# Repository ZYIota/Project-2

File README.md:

# Project-2
This is the Starbie PCB, it is a Printed Circuit Board
It contains multiple components such as the XIAO-ESP32-C3, the MPU-6050 and the DHT11 sensor
I chose to do this project as it was guided and much easier to learn everything from scratch, its relatively low complexity allows me to finish it

This is my PCB layout for the starbie, it contains the electrical wiring and connections for the board (the physical arrangement of components and connectors)
The blue connections means the electrical connections are at the back of the circuit while the red connections means the electrical connections are at the front of the circuit. Connections between components allow communication to occur, hence it is important to connect them according to their ports correctly such as GND to GND and not GND to 5V

This is my schematic layout, it defines the electrical circuit, you can see all the separate components and their pins(GND etc)

This is my 3d layout of the Starbie, it is a render of the PCB layout, it contains the electrical connections and components

FRONT VIEW:

BACK VIEW:

Assembling it requires the pins of correct components matched with the corresponding sections of the PCB, and to physically connect them requires soldering, which uses a soldering iron to melt a solder wire to allow electricity flow while physically sticking to each other

## Bill of Materials (BOM)

| Reference | Qty | Value | Footprint | Datasheet | Price (USD) | Product Link |
|---|---:|---|---|---|---:|---|
| J1 | 1 | Conn_01x04_Pin | Imported Parts:Display_128x64_096_I2C | — | $2.10 | [aliexpress.com/item/1005006141235306.html?spm=a2g0o.cart.0.0.376e38dawU3KcG&mp=1&pdp_npi=6%40dis%21SGD%21SGD%202.89%21SGD%202.69%21%21SGD%202.69%21%21%21%402102ee9117922575991276049e0f0f%2112000035944225406%21ct%21SG%216710596671%21%211%210%21](aliexpress.com/item/1005006141235306.html?spm=a2g0o.cart.0.0.376e38dawU3KcG&mp=1&pdp_npi=6%40dis%21SGD%21SGD%202.89%21SGD%202.69%21%21SGD%202.69%21%21%21%402102ee9117922575991276049e0f0f%2112000035944225406%21ct%21SG%216710596671%21%211%210%21) |
| J2 | 1 | Conn_01x08_Pin | Imported Parts:MPU6050_Module | — | $1.68 | [https://www.aliexpress.com/item/1005010057794277.html?spm=a2g0o.cart.0.0.376e38dawU3KcG&mp=1&pdp_npi=6%40dis%21SGD%21SGD%202.31%21SGD%202.15%21%21SGD%202.15%21%21%21%402102ee9117922575991276049e0f0f%2112000050979433010%21ct%21SG%216710596671%21%211%210%21](https://www.aliexpress.com/item/1005010057794277.html?spm=a2g0o.cart.0.0.376e38dawU3KcG&mp=1&pdp_npi=6%40dis%21SGD%21SGD%202.31%21SGD%202.15%21%21SGD%202.15%21%21%21%402102ee9117922575991276049e0f0f%2112000050979433010%21ct%21SG%216710596671%21%211%210%21) |
| R1 | 1 | 10K | Resistor_THT:R_Axial_DIN0204_L3.6mm_D1.6mm_P7.62mm_Horizontal | — | $2.81 | [aliexpress.com/item/1005010764042202.html?spm=a2g0o.cart.0.0.376e38dawU3KcG&mp=1&pdp_npi=6%40dis%21SGD%21SGD%207.20%21SGD%203.60%21%21SGD%203.60%21%21%21%402102ee9117922575991276049e0f0f%2112000053429025861%21ct%21SG%216710596671%21%211%210%21](aliexpress.com/item/1005010764042202.html?spm=a2g0o.cart.0.0.376e38dawU3KcG&mp=1&pdp_npi=6%40dis%21SGD%21SGD%207.20%21SGD%203.60%21%21SGD%203.60%21%21%21%402102ee9117922575991276049e0f0f%2112000053429025861%21ct%21SG%216710596671%21%211%210%21) |
| SW1,SW2 | 2 | SW_Push | Button_Switch_Keyboard:SW_Cherry_MX_1.00u_PCB | — | $4.24 | [https://www.aliexpress.com/item/1005011598245320.html?spm=a2g0o.cart.0.0.376e38dawU3KcG&mp=1&pdp_npi=6%40dis%21SGD%21SGD+5.43%21SGD+5.43%21%21SGD+5.43%21%21%21%402102ee9117922575991276049e0f0f%2112000056021483980%21ct%21SG%216710596671%21%211%210%21](https://www.aliexpress.com/item/1005011598245320.html?spm=a2g0o.cart.0.0.376e38dawU3KcG&mp=1&pdp_npi=6%40dis%21SGD%21SGD+5.43%21SGD+5.43%21%21SGD+5.43%21%21%21%402102ee9117922575991276049e0f0f%2112000056021483980%21ct%21SG%216710596671%21%211%210%21) |
| U1 | 1 | XIAO-ESP32-C6-DIP | Imported Parts:XIAO-ESP32-C6-DIP | — | $8.52 | [https://www.aliexpress.com/item/1005006946443492.html?spm=a2g0o.cart.0.0.376e38dawU3KcG&mp=1&pdp_npi=6%40dis%21SGD%21SGD%2014.55%21SGD%2010.92%21%21SGD%2010.92%21%21%21%402102ee9117922575991276049e0f0f%2112000058362726009%21ct%21SG%216710596671%21%211%210%21](https://www.aliexpress.com/item/1005006946443492.html?spm=a2g0o.cart.0.0.376e38dawU3KcG&mp=1&pdp_npi=6%40dis%21SGD%21SGD%2014.55%21SGD%2010.92%21%21SGD%2010.92%21%21%21%402102ee9117922575991276049e0f0f%2112000058362726009%21ct%21SG%216710596671%21%211%210%21) |
| U2 | 1 | DHT11 | Sensor:Aosong_DHT11_5.5x12.0_P2.54mm | [http://akizukidenshi.com/download/ds/aosong/DHT11.pdf](http://akizukidenshi.com/download/ds/aosong/DHT11.pdf) | $1.12 | [https://www.aliexpress.com/item/32324748233.html?spm=a2g0o.cart.0.0.376e38dawU3KcG&mp=1&pdp_npi=6%40dis%21SGD%21SGD%201.54%21SGD%201.43%21%21SGD%201.43%21%21%21%402102ee9117922575991276049e0f0f%2166079522736%21ct%21SG%216710596671%21%211%210%21](https://www.aliexpress.com/item/32324748233.html?spm=a2g0o.cart.0.0.376e38dawU3KcG&mp=1&pdp_npi=6%40dis%21SGD%21SGD%201.54%21SGD%201.43%21%21SGD%201.43%21%21%21%402102ee9117922575991276049e0f0f%2166079522736%21ct%21SG%216710596671%21%211%210%21) |
| PCB | 1 | — | — | — | $4.74 | [https://cart.jlcpcb.com/quote?spm=Jlcpcb.Homepage.1006&spm=Jlcpcb.Homepage.1006](https://cart.jlcpcb.com/quote?spm=Jlcpcb.Homepage.1006&spm=Jlcpcb.Homepage.1006) |

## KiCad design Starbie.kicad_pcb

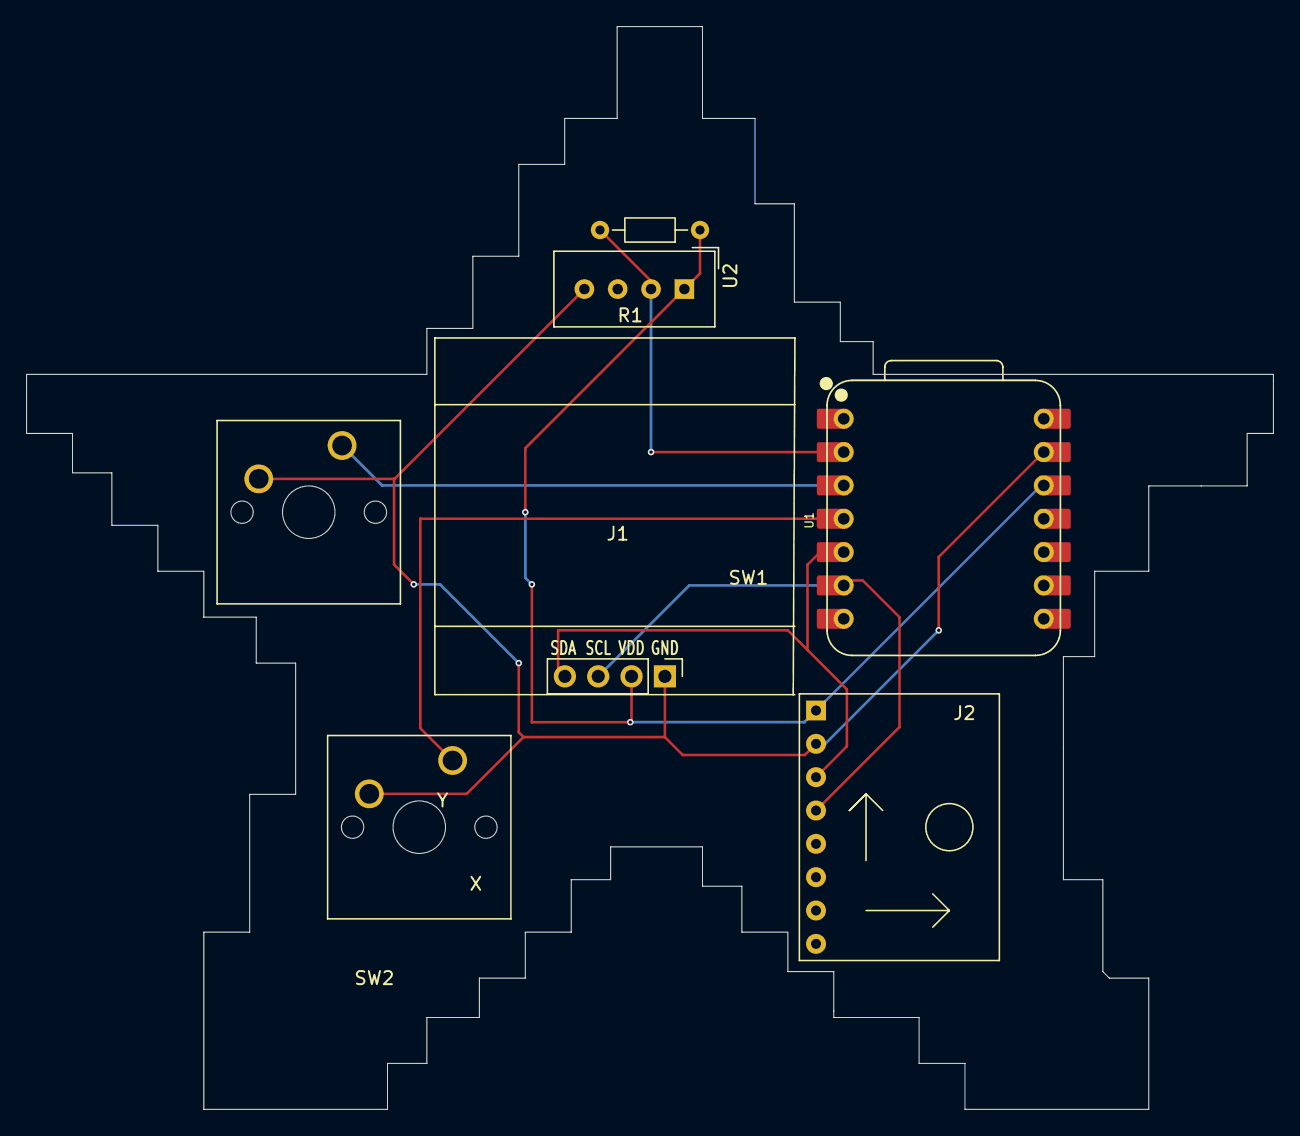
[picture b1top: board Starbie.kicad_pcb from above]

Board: 2 copper layers, 95.0 x 82.5 mm, 7 parts (0 on the bottom side), 7 nets.

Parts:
J1: Conn_01x04_Pin; Display_128x64_096_I2C
J2: Conn_01x08_Pin; MPU6050_Module
R1: 10K; R_Axial_DIN0204_L3.6mm_D1.6mm_P7.62mm_Horizontal
SW1, SW2: SW_Push; SW_Cherry_MX_1.00u_PCB
U1: XIAO-ESP32-C6-DIP
U2: DHT11; Aosong_DHT11_5.5x12.0_P2.54mm

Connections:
+3.3V: J1.2, J2.1, R1.1, U1.12 (3V3_OUT), U2.1 (VDD)
/DHT-11 DATA: R1.2, U1.2 (D1), U2.2 (DATA)
/SCL: J1.4, J2.3, U1.5 (D4)
/SDA: J1.3, J2.4, U1.6 (D5)
/part1: SW1.1, U1.3 (D2)
/part2?: SW2.1, U1.4 (D3)
GND: J1.1, J2.2, SW1.2, SW2.2, U1.13 (GND), U2.4 (GND)
